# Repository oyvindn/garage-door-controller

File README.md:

# Garage door controller

Arduino based garage door controller for ESP32.

Uses MQTT to publish sensor data and to receive the command for triggering the garage door opener.

The 5V relay is used to trigger the garage door opener and the two magnetic door sensors is used to monitor if the door is in the open or closed position.
My garage door opener also has a 5V output for a warning light, which I use to check if the door is in motion.

## Dependencies
* [Arduino core for the ESP32](https://github.com/espressif/arduino-esp32)
* [Arduino Client for MQTT](https://pubsubclient.knolleary.net/index.html)
* [One Wire](https://github.com/PaulStoffregen/OneWire)
* [Arduino Library for Maxim Temperature Integrated Circuits](https://github.com/milesburton/Arduino-Temperature-Control-Library)

## Hardware

* [ESP32-WROOM-32D](https://www.espressif.com/sites/default/files/documentation/esp32-wroom-32d_esp32-wroom-32u_datasheet_en.pdf)
* 2x MC-38 Wired Door Window Sensor
* 5V relay
* Waterproof 1-Wire DS18B20 Compatible Digital temperature sensor

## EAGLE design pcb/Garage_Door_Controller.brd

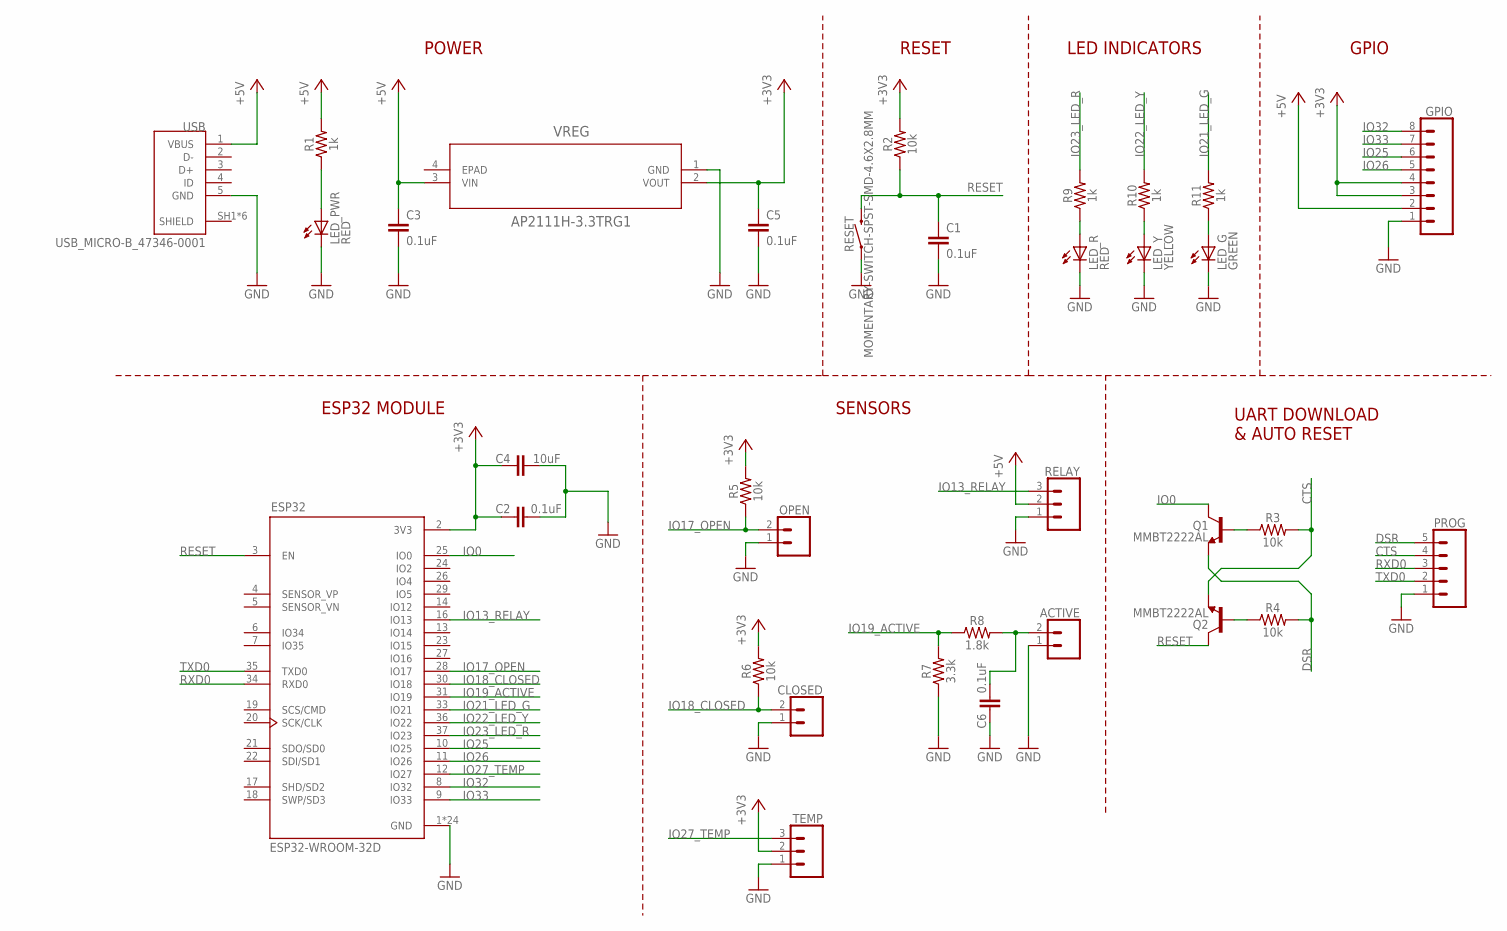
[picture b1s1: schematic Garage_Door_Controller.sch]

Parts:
ACTIVE: CONN_02; 1X02
C1, C2, C3, C5, C6: 0.1uF; 0603
C4: 10uF; 0805
CLOSED: CONN_02; 1X02
ESP32: ESP32-WROOM-32D
GPIO: CONN_08"; 1X08
LED_G: GREEN; CHIPLED_0805
LED_PWR: RED; CHIPLED_0805
LED_R: RED; CHIPLED_0805
LED_Y: YELLOW; CHIPLED_0805
OPEN: CONN_02; 1X02
PROG: CONN_05; 1X05
Q1, Q2: MMBT2222AL; SOT23-3
R1, R9, R10, R11: 1k; 0603
R2, R3, R4, R5, R6: 10k; 0603
R7: 3.3k; 0603
R8: 1.8k; 0603
RELAY: CONN_03; 1X03
RESET: MOMENTARY-SWITCH-SPST-SMD-4.6X2.8MM; TACTILE_SWITCH_SMD_4.6X2.8MM
TEMP: CONN_03; 1X03
USB: USB_MICRO-B_47346-0001; MOLEX_47346-0001
VREG: AP2111H-3.3TRG1; SOT-223_DIO

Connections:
+3V3: C2.1, C4.1, C5.1, ESP32.2 (3V3), GPIO.3, GPIO.4, R2.2, R5.2, R6.2, TEMP.2, VREG.2 (VOUT)
+5V: C3.1, GPIO.2, R1.2, RELAY.2, USB.1 (VBUS), VREG.3 (VIN)
CTS: PROG.4, Q2.2 (E), R3.2
DSR: PROG.5, Q1.2 (E), R4.2
GND: ACTIVE.1, C1.2, C2.2, C3.2, C4.2, C5.2, C6.1, CLOSED.1, ESP32.1 (GND), ESP32.15 (GND), ESP32.38 (GND), ESP32.39_1 (GND), ESP32.39_2 (GND), ESP32.39_3 (GND), ESP32.39_4 (GND), ESP32.39_5 (GND), ESP32.39_6 (GND), ESP32.39_7 (GND), ESP32.39_8 (GND), ESP32.39_9 (GND), ESP32.39_10 (GND), ESP32.39_11 (GND), ESP32.39_12 (GND), ESP32.39_13 (GND), ESP32.39_14 (GND), ESP32.39_15 (GND), ESP32.39_16 (GND), ESP32.39_17 (GND), ESP32.39_18 (GND), ESP32.39_19 (GND), ESP32.39_20 (GND), ESP32.39_21 (GND), GPIO.1, LED_G.C, LED_PWR.C, LED_R.C, LED_Y.C, OPEN.1, PROG.1, R7.1, RELAY.1, RESET.1, RESET.2 (1), TEMP.1, USB.5 (GND), VREG.1 (GND)
IO0: ESP32.25 (IO0), Q1.3 (C)
IO13_RELAY: ESP32.16 (IO13), RELAY.3
IO17_OPEN: ESP32.28 (IO17), OPEN.2, R5.1
IO18_CLOSED: CLOSED.2, ESP32.30 (IO18), R6.1
IO19_ACTIVE: ESP32.31 (IO19), R7.2, R8.1
IO21_LED_G: ESP32.33 (IO21), R11.2
IO22_LED_Y: ESP32.36 (IO22), R10.2
IO23_LED_R: ESP32.37 (IO23), R9.2
IO25: ESP32.10 (IO25), GPIO.6
IO26: ESP32.11 (IO26), GPIO.5
IO27_TEMP: ESP32.12 (IO27), TEMP.3
IO32: ESP32.8 (IO32), GPIO.8
IO33: ESP32.9 (IO33), GPIO.7
unnamed: LED_PWR.A, R1.1
unnamed: Q1.1 (B), R3.1
unnamed: Q2.1 (B), R4.1
unnamed: ACTIVE.2, C6.2, R8.2
unnamed: LED_R.A, R9.1
unnamed: LED_Y.A, R10.1
unnamed: LED_G.A, R11.1
RESET: C1.1, ESP32.3 (EN), Q2.3 (C), R2.1, RESET.3 (2), RESET.4 (2)
RXD0: ESP32.34 (RXD0), PROG.3
TXD0: ESP32.35 (TXD0), PROG.2

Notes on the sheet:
POWER
ESP32 MODULE
RESET
UART DOWNLOAD & AUTO RESET
SENSORS
LED INDICATORS
GPIO

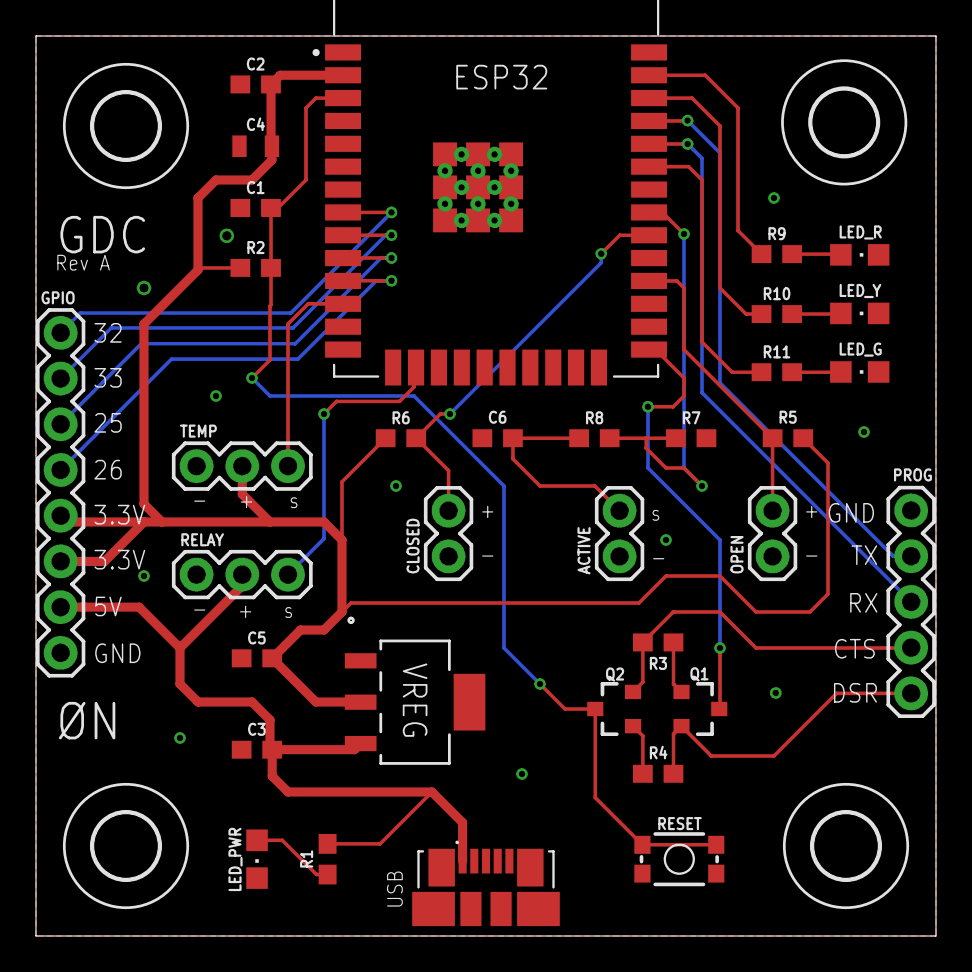
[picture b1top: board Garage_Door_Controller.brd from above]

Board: 2 copper layers, 50.0 x 50.0 mm, 38 parts (0 on the bottom side), 28 nets.

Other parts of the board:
U$1, U$2, U$3, U$4: 3,6

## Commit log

2019-03-18 Pass MQTT client to functions instead of using global referance
2019-03-19 Added mqtt topics and gpio settings
2019-03-27 Changing to 4 space indentation
2019-03-27 Added template for Setup.h
2019-03-27 Better name for message callback
2019-04-10 Added example setup header file
2019-04-11 Ability to trigger the door opener via MQTT
2019-04-11 Read sensor values and publish to MQTT
2019-04-11 Add authentication for MQTT connection
2019-04-20 Authenticate the client with a client certificate
2019-04-20 Updated GPIO pins to match the board prototype
2019-04-20 More precise name
2019-04-20 Forgot to save a file last commit
2019-04-20 Added some more information to the README
2019-04-21 Using auth by client cert
2019-04-21 Forgot to update a name, and removed username og password login for MQTT
2019-04-21 Compare strings, not pointers
2019-04-24 Made a new PCB prototype and changed some of the GPIO pins
2019-04-24 Adding pulldown for sensor inputs to prevent the GPIO from floating
2019-05-02 Sleep for half a second between each loop
2019-05-03 Fixed spelling
2019-05-03 Create LICENSE
2020-03-06 Renamed to camel case naming convention
2020-03-06 Only do serial print when in debug mode
2020-03-06 Renamed setup to config
2020-03-10 Publish current door state instead of raw sensor readings
2020-03-11 Continue to publish raw sensor reading for legacy purposes
2020-03-13 Removed the UNKNOWN state
2020-03-13 Prettifying code
2020-03-13 Added more debug printing to Serial
2020-03-16 Trying a easy fix for flaky sensor values
2020-03-19 New flaky sensor fix that actually works
2020-04-01 No longer publishing raw sensor data to MQTT
2020-05-12 PCB schematic
2020-07-03 Rev A schematics and board layout
2020-07-03 Small change to silkmask do to fab house rendering
2020-10-29 GPIO setup for SMD Rev. A
2020-10-29 Update sensor polling to use new GPIO setup
2020-11-03 Simplify calculation of current door state
2020-11-04 Better naming
2021-01-21 Calculate door state as a normal function
2021-01-21 Remove debug print code
2021-01-21 Ensure that we are connected to Wifi and MQTT before doing any work
2021-01-21 Add config for all timeouts and delays
2021-01-21 Small changes to scheduled tasks
2021-01-21 Rearrang some code
2021-01-21 Add OTA Update
2021-01-21 OTA Update
2021-02-25 Connect to Wifi before setting up OTA Upload
2021-02-25 Do not block main task when waiting to reconnect to MQTT
2021-02-25 Wait time comment
2021-02-26 Update ESP32 chip used in new PCB
2021-03-02 Do not update last door state while the flaky door sensor timer is running
2021-06-11 Add outdoor temperature sensor
2021-06-11 Fix typo
2021-08-19 Reformat code

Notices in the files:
parts and their libraries:
SparkFun-Connectors: Licensing: Creative Commons ShareAlike 4.0 International - https://creativecommons.org/licenses/by-sa/4.0
